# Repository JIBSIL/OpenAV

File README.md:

## OpenAV

### Important Note

OpenAV is still in beta! Please review the schematic, BOM and PCB to adjust the OpenAV kit to your requirements. It is untested so far, so it may have major bugs and other issues.

### Information
The OpenAV PCB was created to be a universal system for rocketry - with a LoRa long distance radio, a SIM800C for geolocation and Internet communication, an ESP32 for WiFi support and an MPU6050 for sensor data, it provides everything you could want in an avionics system. It integrates seamlessly with the OpenAV library to eliminate coding complexity; with a multitude of ready-to-go configurations, it provides support for any kind of rocket.

This project was created with competitive rocketry in mind, and it therefore utilizes optimized algorithms to provide realtime high-accuracy course predictions, even at supersonic speeds. Uncomplicated and open schematics allow for anyone with basic knowledge to add parts to the system (and if you think other people would like it, make sure to open a pull request on our GitHub for it!)

### Using the Project
Currently we have **not** tested the PCB and software's compatibility, so bugs are likely to occur! As we prepare for our first test flight, we will update this repository with fixes and more clear documentation.

Please see the `pcb/` folder for the KiCad 8.0 files and gerbers.

Please see the `software/` folder for information on the OpenAV software and how to run and connect it.

### Affiliations

This project is part of the [7th PCBWay contest](https://www.pcbway.com/project/shareproject/OpenAV_open_source_software_and_hardware_for_DIY_rocketry_1c6062a0.html). If you'd like to support OpenAV's development, please buy the OpenAV PCB from our PCBWay page!

### Contributing
Contributions are welcome and encouraged! If you have something you would like to add, please open a pull request for it!

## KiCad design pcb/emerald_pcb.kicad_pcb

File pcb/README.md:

## OpenAV/pcb

### Information
The gerbers and KiCad 8.0 schematic and PCB files are here. This project will be updated as we evolve to include more sensors and components, and replace old ones. It is functional as it is, and the gerbers are ready to print.

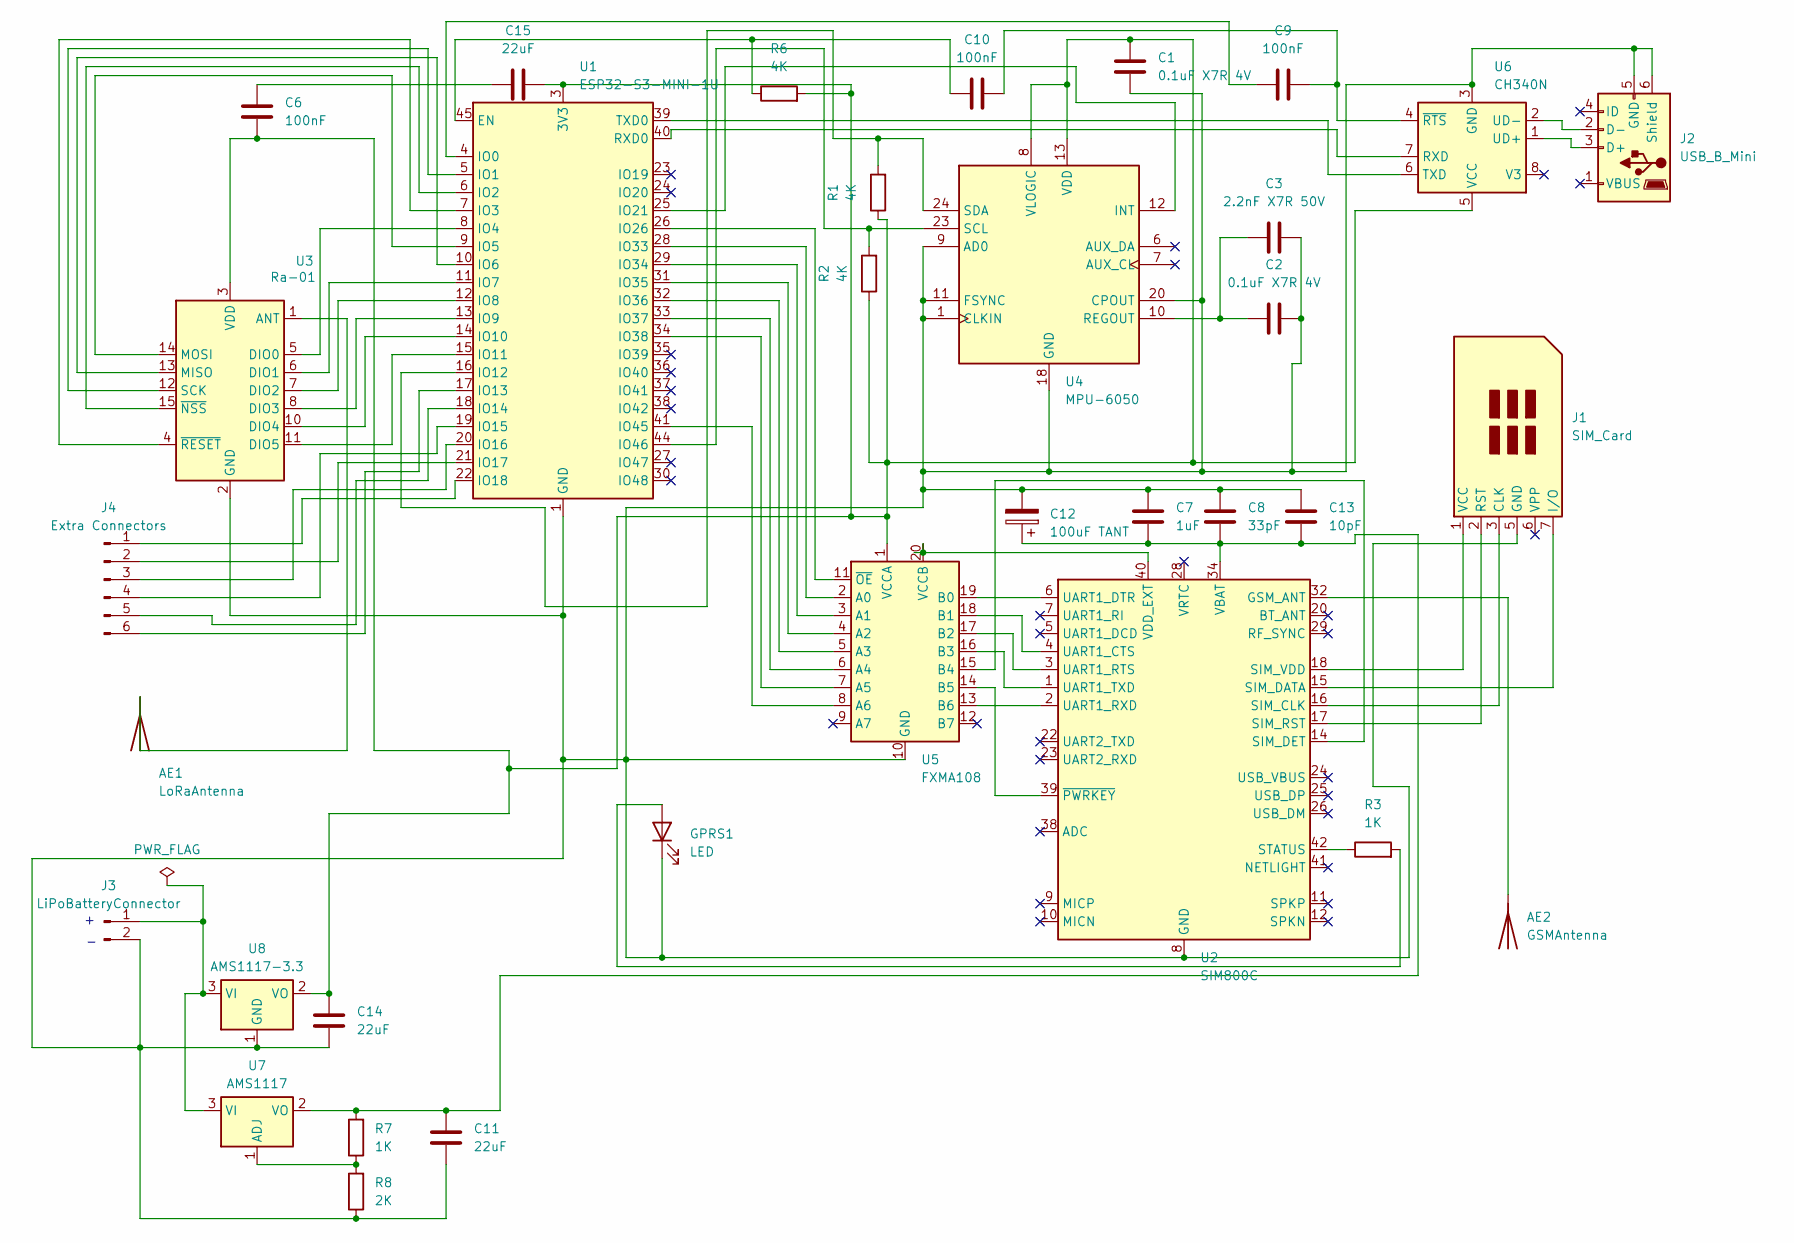
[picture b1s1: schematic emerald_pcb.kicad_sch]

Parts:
AE1: LoRaAntenna; GB042-34S-H10
AE2: GSMAntenna; GB042-34S-H10
C1, C2: 0.1uF X7R 4V; C_0201_0603Metric
C3: 2.2nF X7R 50V; C_0201_0603Metric
C6, C9, C10: 100nF; C_0201_0603Metric
C7: 1uF; C_0201_0603Metric
C8: 33pF; C_0201_0603Metric
C11, C14, C15: 22uF; C_0201_0603Metric
C12: 100uF TANT; C_0201_0603Metric
C13: 10pF; C_0201_0603Metric
GPRS1: LED; LED_0201_0603Metric
J1: SIM_Card; microSIM_JAE_SF53S006VCBR2000
J2: USB_B_Mini; USB_Mini-B_Lumberg_2486_01_Horizontal
J3: LiPoBatteryConnector; AMASS_XT30U-F_1x02_P5.0mm_Vertical
J4: Extra Connectors; PinHeader_1x06_P1.00mm_Vertical
R1, R2, R6: 4K; R_0201_0603Metric
R3, R7: 1K; R_0201_0603Metric
R8: 2K; R_0201_0603Metric
U1: ESP32-S3-MINI-1U; ESP32-S2-MINI-1U
U2: SIM800C; SIMCom_SIM800C
U3: Ra-01; Ai-Thinker-Ra-01-LoRa
U4: MPU-6050; InvenSense_QFN-24_4x4mm_P0.5mm
U5: FXMA108; WQFN-20-1EP_2.5x4.5mm_P0.5mm_EP1x2.9mm
U6: CH340N; SOP-8_3.9x4.9mm_P1.27mm
U7: AMS1117; SOT-223-3_TabPin2
U8: AMS1117-3.3; SOT-223-3_TabPin2

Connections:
unnamed 1: AE1.1, U3.1 (ANT); also elsewhere on the board
unnamed 2: AE2.1, U2.32 (GSM_ANT); also elsewhere on the board
unnamed: C6.2, C15.1
unnamed: GPRS1.2 (A), R3.2
unnamed: C1.1, C2.2, C3.2, C7.1, C8.1, C11.2, C12.2, C13.1, C14.2, GPRS1.1 (K), J1.5 (GND), J2.5 (GND), J2.6 (Shield), J3.2, R8.1, U1.1 (GND), U1.2 (GND), U1.42 (GND), U1.43 (GND), U1.46 (GND), U1.47 (GND), U1.48 (GND), U1.49 (GND), U1.50 (GND), U1.51 (GND), U1.52 (GND), U1.53 (GND), U1.54 (GND), U1.55 (GND), U1.56 (GND), U1.57 (GND), U1.58 (GND), U1.59 (GND), U1.60 (GND), U1.61 (GND), U1.62 (GND), U1.63 (GND), U1.64 (GND), U1.65 (GND), U2.8 (GND), U2.13 (GND), U2.19 (GND), U2.21 (GND), U2.27 (GND), U2.30 (GND), U2.31 (GND), U2.33 (GND), U2.36 (GND), U2.37 (GND), U3.2 (GND), U3.9 (GND), U3.16 (GND), U4.1 (CLKIN), U4.9 (AD0), U4.11 (FSYNC), U4.18 (GND), U4.20 (CPOUT), U5.10 (GND), U6.3 (GND), U8.1 (GND)
unnamed: J1.3 (CLK), U2.16 (SIM_CLK)
unnamed: J1.7 (I/O), U2.15 (SIM_DATA)
unnamed: J1.2 (RST), U2.17 (SIM_RST)
unnamed: J1.1 (VCC), U2.18 (SIM_VDD)
unnamed: J2.3 (D+), U6.1 (UD+)
unnamed: J2.2 (D-), U6.2 (UD-)
unnamed 12: J3.1, U7.3 (VI), U8.3 (VI); also elsewhere on the board
unnamed: J4.1, U1.22 (IO18)
unnamed: J4.2, U1.21 (IO17)
unnamed: J4.3, U1.20 (IO16)
unnamed: J4.4, U1.19 (IO15)
unnamed: J4.5, U1.18 (IO14)
unnamed: J4.6, U1.17 (IO13)
unnamed 19: C1.2, C6.1, C14.1, C15.2, R1.1, R2.1, R6.2, U1.3 (3V3), U3.3 (VDD), U4.8 (VLOGIC), U4.13 (VDD), U5.1 (VCCA), U6.5 (VCC), U8.2 (VO); also elsewhere on the board
unnamed: C10.1, R6.1, U1.45 (EN)
unnamed: C9.1, U1.4 (IO0)
unnamed: U1.5 (IO1), U3.12 (SCK)
unnamed: U1.6 (IO2), U3.15 (~NSS)
unnamed: U1.7 (IO3), U3.4 (~RESET)
unnamed: U1.8 (IO4), U3.5 (DIO0)
unnamed: U1.9 (IO5), U3.14 (MOSI)
unnamed: U1.10 (IO6), U3.13 (MISO)
unnamed: U1.11 (IO7), U3.6 (DIO1)
unnamed: U1.12 (IO8), U3.7 (DIO2)
unnamed: U1.13 (IO9), U3.8 (DIO3)
unnamed: U1.14 (IO10), U3.10 (DIO4)
unnamed: U1.15 (IO11), U3.11 (DIO5)
unnamed: R1.2, U1.16 (IO12), U4.24 (SDA)
unnamed: U1.25 (IO21), U4.12 (INT)
unnamed: U1.26 (IO26), U5.11 (~OE)
unnamed: U1.28 (IO33), U5.2 (A0)
unnamed: U1.29 (IO34), U5.3 (A1)
unnamed: U1.31 (IO35), U5.4 (A2)
unnamed: U1.32 (IO36), U5.5 (A3)
unnamed: U1.33 (IO37), U5.6 (A4)
unnamed: U1.34 (IO38), U5.7 (A5)
unnamed: U1.41 (IO45), U5.8 (A6)
unnamed: R2.2, U1.44 (IO46), U4.23 (SCL)
unnamed: U1.40 (RXD0), U6.7 (RXD)
unnamed: U1.39 (TXD0), U6.6 (TXD)
unnamed: U2.14 (SIM_DET), U5.15 (B4)
unnamed: R3.1, U2.42 (STATUS)
unnamed: U2.4 (UART1_CTS), U5.18 (B1)
unnamed: U2.6 (UART1_DTR), U5.19 (B0)
unnamed: U2.3 (UART1_RTS), U5.17 (B2)
unnamed: U2.2 (UART1_RXD), U5.13 (B6)
unnamed: U2.1 (UART1_TXD), U5.16 (B3)
unnamed: U2.40 (VDD_EXT), U5.20 (VCCB)
unnamed: U2.39 (~PWRKEY), U5.14 (B5)
unnamed: C2.1, C3.1, U4.10 (REGOUT)
unnamed: C9.2, C10.2, U6.4 (~RTS)
unnamed: R7.1, R8.2, U7.1 (ADJ)
unnamed: C7.2, C8.2, C11.1, C12.1, C13.2, R7.2, U2.34 (VBAT), U2.35 (VBAT), U7.2 (VO)

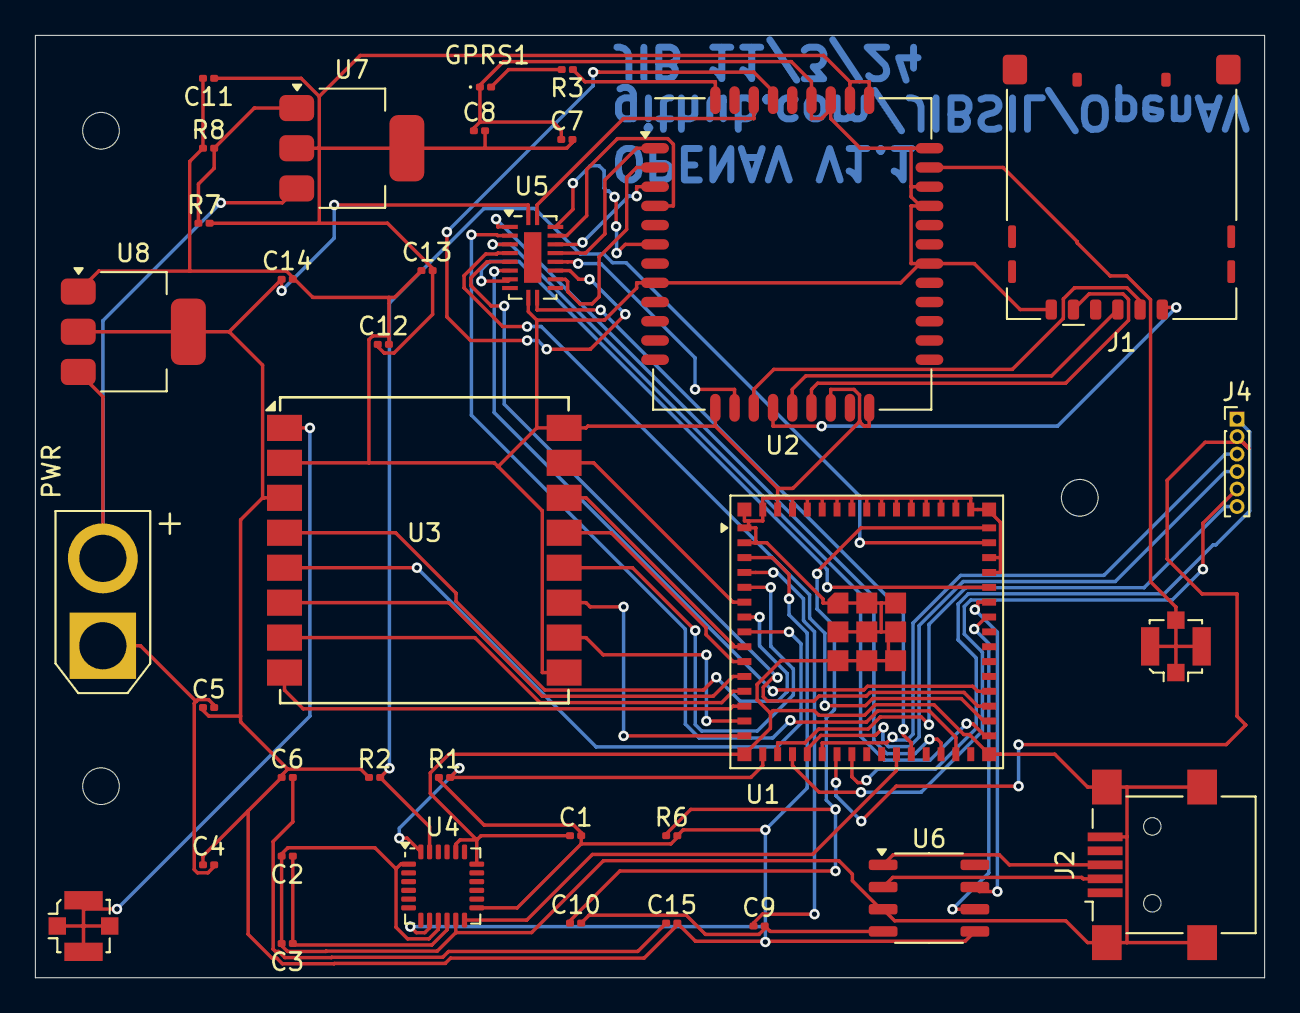
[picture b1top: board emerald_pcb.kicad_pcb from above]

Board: 2 copper layers, 70.3 x 53.9 mm, 39 parts (0 on the bottom side), 59 nets.

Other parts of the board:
ANT1: LoRaAnt; U.FL_Molex_MCRF_73412-0110_Vertical
ANT2: GSMConn; U.FL_Molex_MCRF_73412-0110_Vertical
C4, C5: 100nF; C_0201_0603Metric
PWR: AMASS_XT30U-F_1x02_P5.0mm_Vertical
S1, S2, S3: MountingHole_2.1mm

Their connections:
unnamed: C4.2, C5.2, PWR.1
unnamed 1: ANT1.1, ANT1.2; also elsewhere on the board
unnamed 2: ANT2.1, ANT2.2; also elsewhere on the board
unnamed 12: PWR.2; also elsewhere on the board
unnamed 19: C4.1, C5.1; also elsewhere on the board

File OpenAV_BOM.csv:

OPENAV BOM,"Note: for all suppliers AliExpress is preferred to decrease shipping price, final SUM_PRICE includes minimum quantity of all parts",,,,,,,
,,,,,,,,
PART,TYPE,DEALER,PRICE,LINK,DATASHEET,NOTES,SUM_PRICE,
Lumberg 2486 01,USB connector,AliExpress,1.27 10u,Micro USB 2P 5P Jack Charging Port Plug Dock Charger DIP SMD For Phone Tabletels Speakers etc Port Socket Power Connector - AliExpress 13,Datasheet for 2486 01 Lumberg USB Connectors | Octopart,micro-04,1.27,
ESP32-S3-MINI-1-N8,Main chip,Mouser,3.1 1u,ESP32-S3-MINI-1U-N8 Espressif Systems | Mouser,mouser.com/datasheet/2/891/esp32_s3_mini_1_mini_1u_datasheet_en-2997643.pdf,,3.1,
SIMCOM SIM800C,SIM module,AliExpress,1.9 1u,SIM800C SIM800 Four frequency package Voice SMS data transfer module new original - AliExpress 502,Datasheet for SIM800C Simcom | Octopart,sketchy,1.9,
SX1278,LoRa Transciever,AliExpress,3.26 1u,Ra-01 LoRa SX1278 433M Wireless Spread Spectrum Transmission Module Most Distant 10KM - AliExpress 502,SX1276-7-8.book,,3.26,
MPU6050,Accelerometer,AliExpress,0.71 1u,5pcs/lot MPU-6050 MPU6050 MPU-6052C MPU6052C MPU-9150 MPU9150 MPU-9250 MPU9250 MP92 QFN - AliExpress 502,https://product.tdk.com/system/files/dam/doc/product/sensor/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,obsolete on mouser,0.71,
FXMA108BQX,8 bit digi/analog switcher,Mouser,0.82 1u,FXMA108BQX onsemi / Fairchild | Mouser,"FXMA108 - Dual-Supply, 8-Bit Signal Translator with Configurable Voltage Supplies and Signals Levels, 3-State Outputs and Auto Direction Sensing",,0.82,
CH340N,USB to serial,AliExpress,2.28 5u,5PCS USB To Serial Chip CH340N SOP-8 Built-in Crystal Oscillator - AliExpress 502,Microsoft Word - CH340.doc,,2.28,
UFL Molex,Antenna connector,AliExpress,1.1 20u,10/20/30PCS High Quality UFL Seat IPEX / IPX Connector U.FL-R-SMT RF Coaxial Connectors Antenna 20279-001E - AliExpress 13,,,1.1,
AMS1117-3v3,Voltage regulator,AliExpress,1.08 20u,50PCS AMS1117 3V3 AMS117-3.3 AMS1117 5.0 AMS1117-5.0 SOT223 Voltage Rugulator - AliExpress,Microsoft Word - DS1117,,1.08,
AMS1117-ADJ,Voltage regulator,AliExpress,1.03 20u,50pcs AMS1117 3V3 AMS1117-1.2 AMS1117-1.5 AMS1117-1.8 AMS1117-2.5 AMS1117-3.3 AMS1117-5.0 AMS1117-ADJ SOT223 Voltage Rugulator - AliExpress,Microsoft Word - DS1117,,1.03,
XT30-UPB,Power connector,AliExpress,1.65 1u,Original Amass XT30UPB XT30 UPB 2mm Plug Male Female Bullet Connectors Plugs for RC Lipo Battery - AliExpress 26,n/a,,1.65,
JAE MicroSIM,microSIM,Ali/Mouser,7.71 10u/1.22 1u,10PCS SF53S006VCBR2000 SF72S006VBDR2500 Connectors - AliExpress 502,n/a,SF53S006VCBR2000 JAE Electronics | Mouser,1.22,
,,,,,,,19.42,
Resistor,Resistors,Any (AliExpress),,,,"1k, 2k and 4k resistors needed",,NOTE: resistors and caps are all size 0603 metric
Capacitor,Capacitor,Any (AliExpress),,,,"6x 100nF, 2x 300uF, 1x 2.2nF, 1x 22uF",,

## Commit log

2024-10-19 feat: initial commit of PCB and software
2024-10-19 feat: add readme
2024-10-19 feat: add gerbers to PCB folder
2024-10-19 feat: add readme for pcb and software folders
2024-11-03 feat: update to version 1.1
    Changed power inputs, various schematic changes, added decoupling capacitors, removed rare components
2024-11-03 feat: add BOM and IBOM for v1.1
2024-11-03 feat: add beta note
2025-01-09 feat: added pins to schem. fix: D+ and D- pins being assigned on ESP32
2025-01-09 feat: reroute for fewer vias, simplify design
